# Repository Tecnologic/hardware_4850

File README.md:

# Jacobi
36 V / 45 A (battery side, 100 A peak phase current) drive hardware of the [unimoc](https://github.com/Tecnologic/unimoc)
project, with optimised cooling. Jacobi is the motor controller (logic board and
power board); the firmware lives in the unimoc repository.

| | |
|---|---|
| Board directory (firmware) | `boards/unimoc/jacobi/` |
| Board name | `unimoc_jacobi` |
| Cyphal node name | `org.unimoc.jacobi` |
| EESM variant | Jacobi E |

Formerly `hardware_4850`.

### Naming

The unimoc nodes are named after inventors. Moritz Hermann Jacobi built the
first practical electric motor (1834, Königsberg) and drove a boat on the Neva
with it (1838): the first electric motor put to practical use as a drive, which
is what this board is for.

**Drives**

| Name | Class | Who |
|---|---|---|
| Barlow | small drive | Peter Barlow, whose "Barlow's wheel" (1822) was one of the first electric motors: tiny but turning |
| **Jacobi** | **36 V / 45 A drive (this board, H7)** | Moritz Hermann Jacobi, first practical electric motor (1834) and electric boat on the Neva (1838) |
| Dolivo | big drive | Michail Dolivo-Dobrowolsky invented the three-phase motor and the three-phase system (AEG, 1889), the basis of every FOC drive |

**Other nodes**

| Name | Role | Who |
|---|---|---|
| Zuse | VDC | Konrad Zuse built the first working programmable computer, so he's the brain |
| Drais | Pedal generator | Karl Drais invented the Laufmaschine (1817), the ancestor of the bicycle, powered by your own feet |
| Mercator | Steering | the map maker everyone navigates by |
| Gutenberg | Display | made information visible to everyone |
| Volta | BMS / battery | invented the battery (the voltaic pile, 1800) |
| Otto | Throttle | Nikolaus Otto, of the Otto engine: the classic gas pedal |

## Ratings and limits

What the hardware can do and where it stops. The numbers come from the
datasheets and rough loss and thermal estimates (calculations below), not from
measurements on a test bench. The reference load is the kids' quad: an MY1020
1600 W BLDC on 3 × 12 V lead-acid, which the controller already drives with
80 A peak phase current.

| | Rating | Limited by |
|---|---|---|
| Battery | **3 × 12 V lead-acid (36 V)**, up to 44 V while charging; Li-ion up to 10S (42 V) | 60 V FETs (NCEP6080AG), see below |
| Enable input (J501 pin 3 against pin 4) | **12–40 V**, switched battery voltage; 1–4 mA through a TLP291 optocoupler, 3750 Vrms isolation | input resistor R1115 (10k, 1206): 0.19 W at 44 V, 0.25 W rating |
| Battery current | **~45 A** (1600 W at 36 V) for minutes in still air; continuous only with better cooling | housing to air: 1600 W needs about 58 A peak phase current |
| Phase current, peak | **100 A** for seconds | motor saturation, FET losses |
| Phase current, continuous | **~50 A peak** in still air; with the housing bolted to a frame or in airflow, the 100 A motor limit comes first | housing to air (about 2.5 K/W) |
| Overcurrent trip | **120–130 A** | current sensing range ±160 A |
| Not suitable for | 48 V systems (13S/14S Li-ion, 4 × 12 V lead-acid) | 60 V FET rating |

### Target motors

| Motor | Saturation (peak phase current) | Fit |
|---|---|---|
| 60 mm stator motors | ~100 A | up to the rating |
| Hoverboard hub motors | ~55 A | about a third of the current range, fine resolution |
| MY1020 1600 W, 36 V (kids' quad) | not published, estimated 80–100 A | runs today at 80 A peak |

The MY1020 has no published saturation data. It can be measured with the
controller: lock the rotor, run a DC current on the d or q axis in steps
(0, 20, 40 … 120 A) and measure L = V / (di/dt) with a small voltage pulse.
Saturation starts where L falls by 20–30 %. Above that current the motor gives
little extra torque and mostly heat, so it is the useful current limit.

### Bridge voltage: why 36 V

The bridge uses **NCEP6080AG** (NCE, LCSC `C182469`, DFN5×6-8L), two in
parallel per switch, 12 per board. They are in stock and cost much less than
an 80 V part. From the LCSC product page (the datasheet PDF was not
reachable): 60 V, 80 A, R_DS(on) < 4.0 mΩ at 10 V (3.5 mΩ typ),
< 5.0 mΩ at 4.5 V, Qg 67 nC, Coss 680 pF, 85 W, Tj up to 150 °C.

| Battery | Max voltage | Margin to 60 V |
|---|---|---|
| 3 × 12 V lead-acid | ~44 V (charging) | 16 V: **fine** |
| 10S Li-ion | 42 V | 18 V: **fine** |
| 13S Li-ion | 54.6 V | 5 V: switching overshoot alone can use that, **no** |
| 14S Li-ion / 4 × 12 V | 58.8 V / ~58 V | **no** |

For 48 V the bridge needs 80 V FETs in the same footprint, e.g. the Infineon
**BSC040N08NS5** (80 V, 4.0 mΩ max, 121 A, marking `040N08NS`), which sits on
one of the existing prototype boards. Its R_DS(on) is the same as the NCE part;
its lower gate charge (43 nC) only shortens the switching edges a little. The
rest of the board already handles 48 V: the LM5008 supply runs from the battery
up to 95 V, and the voltage dividers reach 73.8 V full scale.

### Bridge losses

Two FETs in parallel per switch, sine current, 36 V, 20 kHz PWM, about 45 ns
switching edges (LM5109B at about 1 A into 2 × 67 nC, 1R1 gate resistors).
R_DS(on) is 4.0 mΩ max × 1.6 for Tj = 125 °C ≈ 6.4 mΩ. The factor 1.6 is
taken from the BSC040N08NS5 curve because the NCE datasheet was not
available; check it once the datasheet is in `datasheets/`.

| Phase current (peak) | Loss per FET | Loss per phase | Whole bridge |
|---|---|---|---|
| 50 A | ~1.3 W | ~5 W | ~16 W |
| 80 A | ~3 W | ~12 W | ~36 W |
| 100 A | ~4.5 W | ~18 W | ~54 W |

Conduction per FET is I_rms² × R_DS(on) / 8 (the phase current splits over two
FETs, and high and low side each conduct about half the time). Switching per
phase is ½ × V × I_avg × (t_on + t_off) × f_PWM with I_avg = 2/π × I_peak.

Using one FET per switch instead of two would save 6 FETs and about 180 mm²,
but it doubles the conduction loss at the same current (about 16 W per FET at
100 A peak). In the closed housing that comes straight off the continuous
current, so the board keeps two per switch.

### PCB manufacturing

The board is made by JLCPCB: 4 layers, **1 oz copper** on all layers (outer and
inner), standard process. The design rules in `jacobi.kicad_pro` follow the
[JLCPCB 4-layer capabilities](https://jlcpcb.com/capabilities/pcb-capabilities):

| Rule | Value |
|---|---|
| Min track width / clearance | 0.1 mm / 0.1 mm |
| Min via (diameter / drill) | 0.45 mm / 0.2 mm, annular ring 0.125 mm |
| Min copper to board edge | 0.3 mm |
| Min hole to hole / hole clearance | 0.25 mm |
| Min silk text | 1.0 mm high, 0.15 mm line |

Net classes set the routing defaults (the high-current nets use pours, the track
width is only for stubs and pad entries):

| Class | Track / clearance / via | Nets |
|---|---|---|
| Power | 1.0 / 0.25 / 0.8 ⌀ 0.4 mm | +BATT, GNDPWR, phase and switch nodes |
| GateDrive | 0.5 / 0.2 / 0.6 ⌀ 0.3 mm | +12P, gate, HO/LO/HS/VSS, bootstrap |
| Dig Supply | 0.4 / 0.2 / 0.6 ⌀ 0.3 mm | +12V, +3V3, +1V2, +BATT_LOGIC, GNDD, buck nodes |
| Analog Supply | 0.4 / 0.2 / 0.6 ⌀ 0.3 mm | +3.3VA, +3.3VADC, GNDA, GND |
| Analog | 0.2 / 0.2 / 0.45 ⌀ 0.2 mm | current and voltage sense, temperature, ADC inputs |
| USB | 0.2 / 0.2 mm, pair gap 0.15 mm | USB_DP, USB_DM (impedance not yet checked) |
| Default | 0.15 / 0.15 / 0.45 ⌀ 0.2 mm | everything else |

### Cooling

The power board sits on an aluminium block the size of the board, which is
mounted to the floor of the G113T housing (115 × 90 mm). Today the bottom
copper is covered by solder mask, with thermal paste to the block and a
thermal pad to the housing.

| Step (per FET unless noted) | Rth | Note |
|---|---|---|
| Junction → case | ~1 K/W | datasheet class value |
| **Thermal vias** | **~3.3 K/W** | 38 × 0.4 mm, 25 µm plating: the largest step from FET to block |
| Solder mask + paste | ~1 K/W | 20 µm mask, 50 µm paste over about 100 mm² |
| Junction → block | **~5.5 K/W** | about 17 K at 80 A peak, about 25 K at 100 A peak |
| Block → housing (pad, whole board) | 0.05–0.1 K/W | 3–5 K at 54 W |
| **Housing → air (whole board)** | **~2–3 K/W** | 0.043 m² of housing in still air: **sets the continuous current** |

At 80 A peak the bridge loses about 36 W. In still air the housing would end up
far above any sensible temperature; it works because the peaks are short. The
block and housing hold about 600 J/K (10 mm block assumed), a time constant of
about 25 minutes, so 54 W (100 A peak) heats them by about 5 K per minute.

Continuous current for a block at ≤ 80 °C at 40 °C ambient (40 K):

| Housing to air | Allowed loss | Continuous phase current |
|---|---|---|
| Still air, ~2.5 K/W | ~16 W | ~50 A peak |
| Bolted to the frame or in airflow, ~0.5 K/W | ~80 W | ~120 A peak, so the 100 A motor limit comes first |

Improvements, biggest first:

1. **Housing to air.** Bolt the housing to the vehicle frame or a metal plate
   with paste, or add fins or airflow. This is worth more than all other steps
   together.
2. **Thermal vias.** Filled and capped vias (VIPPO) under the drain pad, as many
   as fit: about half the 3.3 K/W. The board stays 1 oz copper; the currents are
   carried by pours on all four layers, not by thicker copper.
3. **Block to housing.** Thin paste on flat surfaces instead of the thermal pad,
   screws near the FET rows.
4. **Copper spreading.** Large drain pours under each FET on the bottom and
   inner layers.

**Keep the isolation.** The bottom copper under the high-side FETs is at
+BATT, under the low-side FETs it is the phase node, and the block conducts.
The solder mask is the only insulation today. Opening the mask needs a defined
insulator instead (25 µm polyimide film or a 0.15–0.2 mm ceramic-filled pad);
thermally that is about the same as mask and paste, but the isolation is
reliable. Avoid metal-filled pastes there.

### Current sensing

One 0.5 mΩ 3920 shunt per phase (Yezhan DSLR-M-5-0.5F) in the phase output,
with an INA240A1 (gain 20):

| | |
|---|---|
| Range | 1.6 V / (20 × 0.5 mΩ) = **±160 A**, 10 mV/A |
| Overcurrent trip | 120–130 A, above the 100 A motor saturation |
| Offset | 25 µV max at the input = 0.05 A; calibrated at start, drift 0.25 µV/K |
| Resolution | about 0.08 A at 12 effective bits |
| Shunt loss | 1.6 W at 80 A peak, 2.5 W at 100 A peak (9 W part) |

Other combinations that were considered:

| Shunt + INA240 | Range | Why not |
|---|---|---|
| 0.4 mΩ + A1 | ±200 A | only needed for currents above 130 A, which the motors cannot use |
| 0.2 mΩ + A2 | ±160 A | same scaling, but 2.5× the offset in amps, and the A2 costs 1.60 € vs 0.25 € for a shunt |
| 0.2 mΩ + A1 | ±400 A | coarse at light load (about 0.2 A noise) |

## KiCad project

The logic board and the power board are combined in a single **KiCad 10** project:
[`jacobi.kicad_pro`](jacobi.kicad_pro).

| File | Content |
|---|---|
| [`jacobi.kicad_sch`](jacobi.kicad_sch) | Root sheet with the two board sheets |
| [`logic.kicad_sch`](logic.kicad_sch) | Logic board: sub-sheets [`power_supply`](power_supply.kicad_sch) and [`controller`](controller.kicad_sch); `controller` has the sub-sheets [`interfaces`](interfaces.kicad_sch) and [`analog`](analog.kicad_sch) |
| [`power.kicad_sch`](power.kicad_sch) | Power board: sub-sheet [`phase`](phase.kicad_sch), used three times for phase A/B/C |
| [`jacobi.kicad_pcb`](jacobi.kicad_pcb) | Both boards side by side: logic board on the left, power board on the right |
| [`footprints/jacobi.pretty`](footprints/jacobi.pretty) | Project footprint library: enclosure RND 455-00370, the Kelvin footprint of the phase shunt `R_Shunt_Yezhan_DSLR-5_3920_Kelvin`, and `LFPAK56_ThermalVias-1` and `C_2220_5650Metric`, which KiCad 10 no longer ships |

Since both boards are in one PCB file, the net names are kept apart by the
schematic hierarchy (`/logic/...`, `/power/...`). The board-to-board connectors
(J101/J102/J111 on the logic board, J103/J104/J110 on the power board) are **not** joined
electrically in the schematic, so each board keeps its own nets.

## Schematic ahead of the PCB

The schematic is ahead of the PCB. The logic board will be laid out again;
the PCB still shows the old F730 board.

- **MCU: STM32H743VIT6** (LQFP100, 2 MB flash, LCSC `C114409`) instead of the
  STM32F730R8. It sits on the `controller` sheet (now A3) and connects by net
  labels; the old wires end in labels of the same names. Added decoupling
  C613–C622; C603 is now 2.2 µF (VCAP). Pin plan and open points:
  [docs/h743_logic_board.md](docs/h743_logic_board.md).
- **Simple analog front end.** The op-amp filters of the logic board are gone
  (the three `current_filters` sheets with low pass and AC high pass per phase,
  and the U701 filters for Vdc and the bridge NTC). What is left on the `analog`
  sheet:
  - Ia/Ib/Ic: 220R / 2n2 RC from the INA240 outputs (R717–R719, C713–C715)
  - Va/Vb/Vc: 220R / 2n2 RC (R720–R722, C716–C718), the same as the currents
  - Vdc: 4k7 / 10n RC (R705/C704)
  - +12P (gate driver supply): 4k7 / 10n RC (R723/C719)
  - bridge NTC: pull-up R703 with C701, then a 4k7 / 10n RC (R704/C703)
  - motor temperature unchanged

  The filter values are a first guess.
- **Voltage sensing on the power board.** The dividers for the phase voltages
  and Vdc (47k / 2k2 0.1 %, with 1 nF; R101–R108, C101–C104) sit on the power
  board and go to the logic board over a third 2×5 connector, J110 → J111
  (VSENSE). The old Vdc divider R701/R702/C702 on the logic board is gone.
- **Gate driver supply sense.** A 10k / 2k2 divider (R109/R110, C105) on +12P
  at the drivers goes over pin 3 of the PWM connector (J103 → J101) to PC5. No
  12 V is routed to the analog part.
- **Power board present.** J110 pin 9 is GND on the power board; on the logic
  board it is pulled up (R612, 10k) to PE4 (`PWR_DET`, low = present).
- **Bridge NTC to GND on the power board.** TH101 has its low side on the power
  board GND; only the high side goes through J104 pin 8. J104 pin 10 is now GND.
- **One shunt per phase.** 0.5 mΩ 3920 (Yezhan DSLR-M-5-0.5F, LCSC
  `C41382689`) with Kelvin sense pads instead of three 2 mΩ 2512 in
  parallel, read by an INA240A1 (gain 20): ±160 A.
- **USB-C** instead of mini-B: HRO TYPE-C-31-M-12 (LCSC `C165948`, 16 pins,
  USB 2.0), 5k1 on CC1/CC2 (R613/R614) as a device. SBU not connected.
- **PWM_EN through an optocoupler.** The PWM_EN jumper J1102 is gone. The
  enable input is a TLP291 (U1102) on the `interfaces` sheet that pulls PE15
  high. J501 (`Enable`, now 4-pin JST PH) carries, from pin 1: `+BATT_LOGIC`
  (battery +), the LM5008 supply (VIN), `PWM_EN_IN` (opto LED +, **12–40 V**)
  and `PWM_EN_RTN` (opto LED return, battery −). The LED path is 10k (R1115)
  with 10n (C1108) across the LED and a 1N4148W (D1105) against reverse
  polarity. The output has a 510R collector resistor, a 10k pulldown (R1116)
  and 10n (C1109). `PWM_EN_RTN` is not connected to `GNDD`, so the enable
  line is isolated and its current stays in its own wire pair, which keeps
  noise out on a cart with four drives. Keep the LED side clear of copper from
  the output side under U1102 (5 mm creepage). On the bench bridge pins 1–2,
  put battery + on pin 3 and battery − on pin 4. On the cart switch pin 2
  (logic) and pin 3 (phases).
- **`+48V` is now `+BATT_LOGIC`.** The board is no longer 48 V compatible
  (60 V FETs), so the logic board supply net (J101 pin 1, J501 pin 1) is named
  after the battery. It stays a separate net from `+BATT` on the power board.
- **No aux bridge.** The EESM excitation and brake chopper are out of scope for
  this board; a separate module will do that.

## Production data

The production files of the PCB contain both boards. For separate production
data per board, the old KiCad 5 data is in
[`production/legacy_kicad5/`](production/legacy_kicad5) (as manufactured, with
the op-amp filters, and the 2020 logic board BOM with prices).

## Other folders

| Folder | Content |
|---|---|
| [`datasheets/`](datasheets) | Component datasheets |
| [`docs/`](docs) | Pictures of the [logic board](docs/logic_board.png) and the [power board](docs/power_board.png) (old F730 boards), [H743 logic board concept](docs/h743_logic_board.md) |
| [`mechanical/`](mechanical) | DXF exports of the power board, the cooler drawing, [`enclosure/`](mechanical/enclosure) with STEP and DXF views of the RND 455-00370 |
| [`nucleo_adapter/`](nucleo_adapter) | Bench adapter: a NUCLEO-H743ZI drives the legacy 4850 power board in place of the old logic board (own KiCad project, see its [README](nucleo_adapter/README.md)) |

## Conversion notes (KiCad 5.1 → KiCad 10)

- All symbols are updated from the KiCad 10 library; no KiCad 5 symbol
  graphics are left. The unused `SolderJumper_2_Open` was dropped. The old
  bitmaps of the other board on the `logic` and `power` sheets are removed.
- The KiCad 5 schematic had other values than the PCB on the power board (the
  PCB was changed later). The schematic now follows the PCB: Q`x`01–Q`x`04
  `NCEP6080AG`, C`x`07/C`x`09 `56u`, R`x`03–R`x`10 `1R1`. Their old `Part#`
  order numbers were removed and still have to be filled in.
- Parts that KiCad 10 dropped or renamed:
  - Footprints `LFPAK56_ThermalVias-1` and `C_2220_5650Metric` are now in the
    project library, copied from the PCB.
  - The 3D model of the 2220 capacitor now points to `C_2220_5750Metric`.
  - Symbols are relinked: `Device:CP` → `Device:C_Polarized`,
    `Device:Ferrite_Bead_Small` → `Device:FerriteBead_Small`,
    `Device:Jumper_NO_Small` → `Jumper:Jumper_2_Small_Open`.

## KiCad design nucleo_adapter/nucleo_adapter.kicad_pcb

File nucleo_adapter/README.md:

# Nucleo adapter for the legacy 4850 power board

A bench adapter that lets a **NUCLEO-H743ZI** (first revision, MB1137, silicon
rev. Y) drive the **legacy 4850 power board**, the one ordered on 2019-11-20
(`production/legacy_kicad5/power`). It takes the place of the old STM32F730
logic board, so the H7 hot path of the unimoc firmware can run against the
real INA240 stage before Jacobi exists. The power stage itself is not part of
this design.

KiCad 10 project: `nucleo_adapter.kicad_pro`. Status: **draft, not routed, not
reviewed**. The schematic and the PCB are generated (see `tools/`) and pass
ERC and DRC with schematic parity. Only the 167 unrouted connections are left.

## What lines up with the power board

The PCB uses the coordinate system of the legacy power board, so you can
overlay the two files (`production/legacy_kicad5/power`, KiCad 5 PCB of commit
`d914cf3`, which matches the Gerbers exactly).

| Adapter | Power board | Position (mm) | Note |
|---|---|---|---|
| J101 PWM, SMD 2x05 pin header, bottom | J103, SMD 2x05 socket | (64.5, 120.75), rot 90 | Copied from the old logic board's J101 |
| J102 ADC, SMD 2x05 pin header, bottom | J104, SMD 2x05 socket | (125.0, 130.0), rot -90 | Copied from the old logic board's J102 |
| H101, M3 | H105 | (99.75, 106.75) | Standoff |
| H102, M3 | H104 | (70.0, 178.5) | Standoff |
| H103, M3 | H107 | (122.0, 178.5) | Standoff |
| (no hole) | H106 | (100.25, 157.5) | Heatsink bolt; outline on `User.Drawings` |

These footprints are locked. The generator checked every pad against the old
logic board and every pin against the power-board socket: all 20 pins mate
with the intended signal (table below). The power-board area keeps the old
logic board's 8 x 8 mm notches at the far corners. `User.Drawings` shows the
84 x 79 mm power-board outline.

The current Jacobi PCB keeps the holes H101-H107 where they were, but moves
J101/J102 and adds J110/J111 (VSENSE). **This adapter fits only the legacy
power board.**

### Connector pinout (from the as-ordered power board)

| Pin | J101 PWM | | J102 ADC | |
|---|---|---|---|---|
| 1 | +BATT (DC link, only sensed here) | | +3.3VA (INA240 V+ and REF2) | |
| 2 | GND (= GNDPWR) | | I_C | INA240 out, phase C |
| 3 | open on the power board | | GNDA (power-board GND) | |
| 4 | PWM_AH | LM5109B HI, phase A | I_B | |
| 5 | +12V (gate driver VDD, from the adapter) | | GNDA | |
| 6 | PWM_AL | | I_A | |
| 7 | PWM_CL | | GNDA | |
| 8 | PWM_BH | | T_BRIDGE (NTC TH101, high side) | |
| 9 | PWM_CH | | GNDA | |
| 10 | PWM_BL | | GNDA (NTC low side) | |

INA240A1 on the power board: V+ and REF2 on +3.3VA, REF1 on GND, so
`I_x = 1.65 V + 20 mV/A`. With two 2 mΩ shunts in parallel per phase that is
about ±80 A full scale. No scaling is needed for the 3.3 V ADC.

## Board

- Outline: 100 x 221 mm in total. The power-board area is x 57..141,
  y 103..182 (84 x 79). The Nucleo part is x 49..149, y -39..103.
- 4 layers, with the design rules and the default net class of Jacobi (JLCPCB
  4-layer).
- The Nucleo (`U201`, footprint `Module:ST_Morpho_Connector_144_STLink_MountingHoles`)
  sits on the top side in two **2 x 36 female morpho sockets** (CN11, CN12).
  Footprint pads 1-144 are the symbol pins. Pads 145-148 at the ST-LINK end
  are not in the symbol: leave them empty.
- The morpho pins end 19 mm before the power-board edge, so no pin points
  down into the power stage. The ST-LINK USB is at the free end. The Nucleo's
  RJ45 end overhangs the power-board area above the adapter.
- Edge connectors (placed, not locked): J601 12 V in, J401 ENABLE, J503 HALL,
  J301 MOT_TEMP, J302 VPHASE on the left; J501/J502 CAN on the right.
- All other parts are parked to the right of the board, one column per sheet.

## Schematic

All sheets are A4. Hierarchy: root overview, then `power_board`, `nucleo`
(portrait), `analog` (currents, NTCs), `voltage` (Vdc and phase voltages),
`gate`, `interfaces` (CAN FD, Hall) and `supply`.

| Function | Nucleo pin | Circuit |
|---|---|---|
| PWM A/B/C high, low | PE9, PE11, PE13 / PE8, PE10, PE12 (TIM1) | 100R series, 10k pull-down at J101 |
| Break / enable | PE15 (TIM1_BKIN) | J401: close the loop to release; open = all outputs off |
| Ia, Ib, Ic | PA6, PB1, PC2_C | 220R / 2n2 |
| Vdc | PC3_C | 47k / 2k2 0.1 %, 1n (73.8 V full scale) |
| Va, Vb, Vc | PF11, PF13, PF10 | Same dividers, from J302 (wires to the phase pads J106-J108) |
| Bridge / motor temperature | PF12 / PF14 | 10k pull-up to +3.3VA, 1k / 100n |
| Hall A/B/C | PD12, PD13, PD14 | 2k2 pull-up to +3V3, 1k / 1n, sensors on +5V |
| CAN FD | PD0 RX, PD1 TX (FDCAN1) | TCAN334, JST GH 4 (Cyphal micro), 120R on JP501 |

The pin map is the one in the unimoc firmware,
`app/boards/nucleo_h743zi.overlay` on branch `hardware/first-startup`.

Supplies:

- **+12V** for the gate drivers comes from a bench supply on J601 (SS34
  reverse protection, SMAJ15CA clamp). It does not come from the DC link,
  because the first power-on runs the DC link at 12 V / 0.5 A.
- **+3.3VA** comes from the Nucleo +3V3 (VDDA, the ADC reference) through
  FB601, so the INA240 offset tracks the ADC reference.
- **GND and GNDA** meet only at FB602, as at FB502 on the old logic board. The
  power board does not join GND (GNDPWR) and its analog GND.

## To check before layout

1. LM5109B input threshold against 3.3 V logic (VIH in the datasheet).
2. Filter values (220R / 2n2, 1k / 100n) are first guesses.
3. Clearance under the adapter: the old logic board had the same stack height
   (SMD socket on the power board, SMD header on the bottom here). The
   bottom side over the power board should stay free of tall parts.
4. Mounting-hole and standoff heights against the socket height of J103/J104.
5. Whether J101 pin 3 should carry anything. It is open on the power board.
6. Phase-voltage wires on J302: only needed for identification step I3.
7. Firmware: the Nucleo overlay has no `PWM_EN` GPIO. Here the enable is the
   break loop on PE15.

## Tools

`tools/` holds the one-shot generator that made the first version:
`design.py` (the netlist as data), `gen_sch.py`, `gen_pcb.py` (KiCad 10
pcbnew), `gen_pro.py`, `checknet.py`. The KiCad files are the source from now
on. Edit them in KiCad and do not regenerate over manual work.

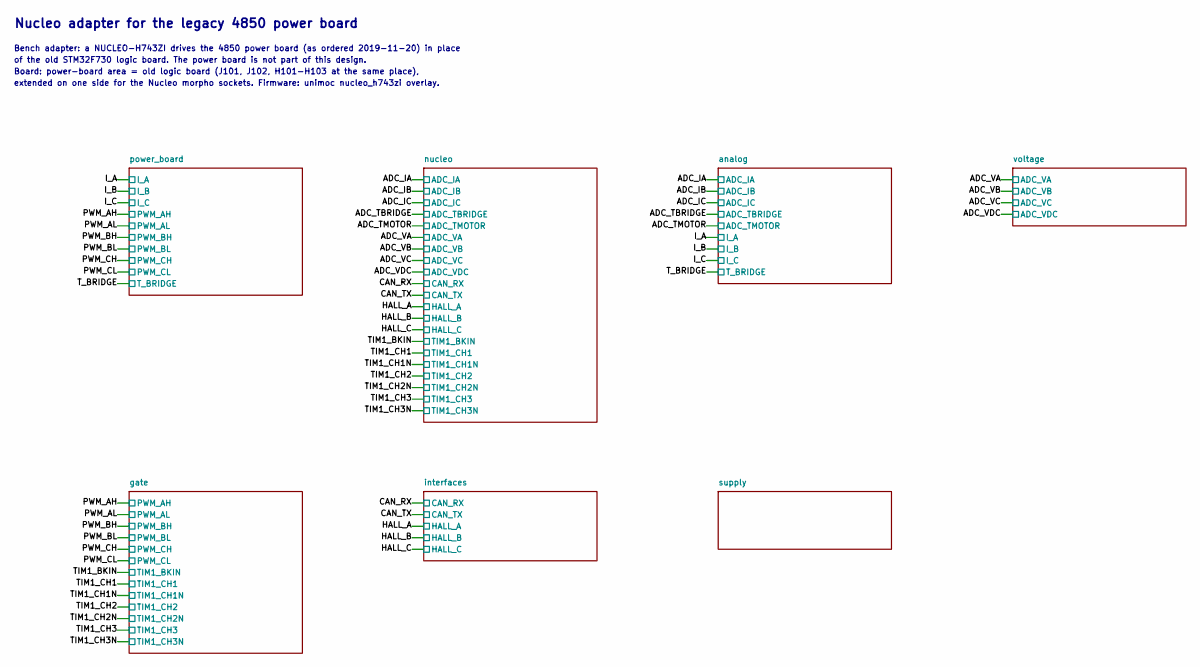
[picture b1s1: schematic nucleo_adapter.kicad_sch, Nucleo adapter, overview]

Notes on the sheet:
Bench adapter: a NUCLEO-H743ZI drives the 4850 power board (as ordered 2019-11-20) in place
of the old STM32F730 logic board. The power board is not part of this design.
extended on one side for the Nucleo morpho sockets. Firmware: unimoc nucleo_h743zi overlay.
Nucleo adapter for the legacy 4850 power board
Board: power-board area = old logic board (J101, J102, H101-H103 at the same place),

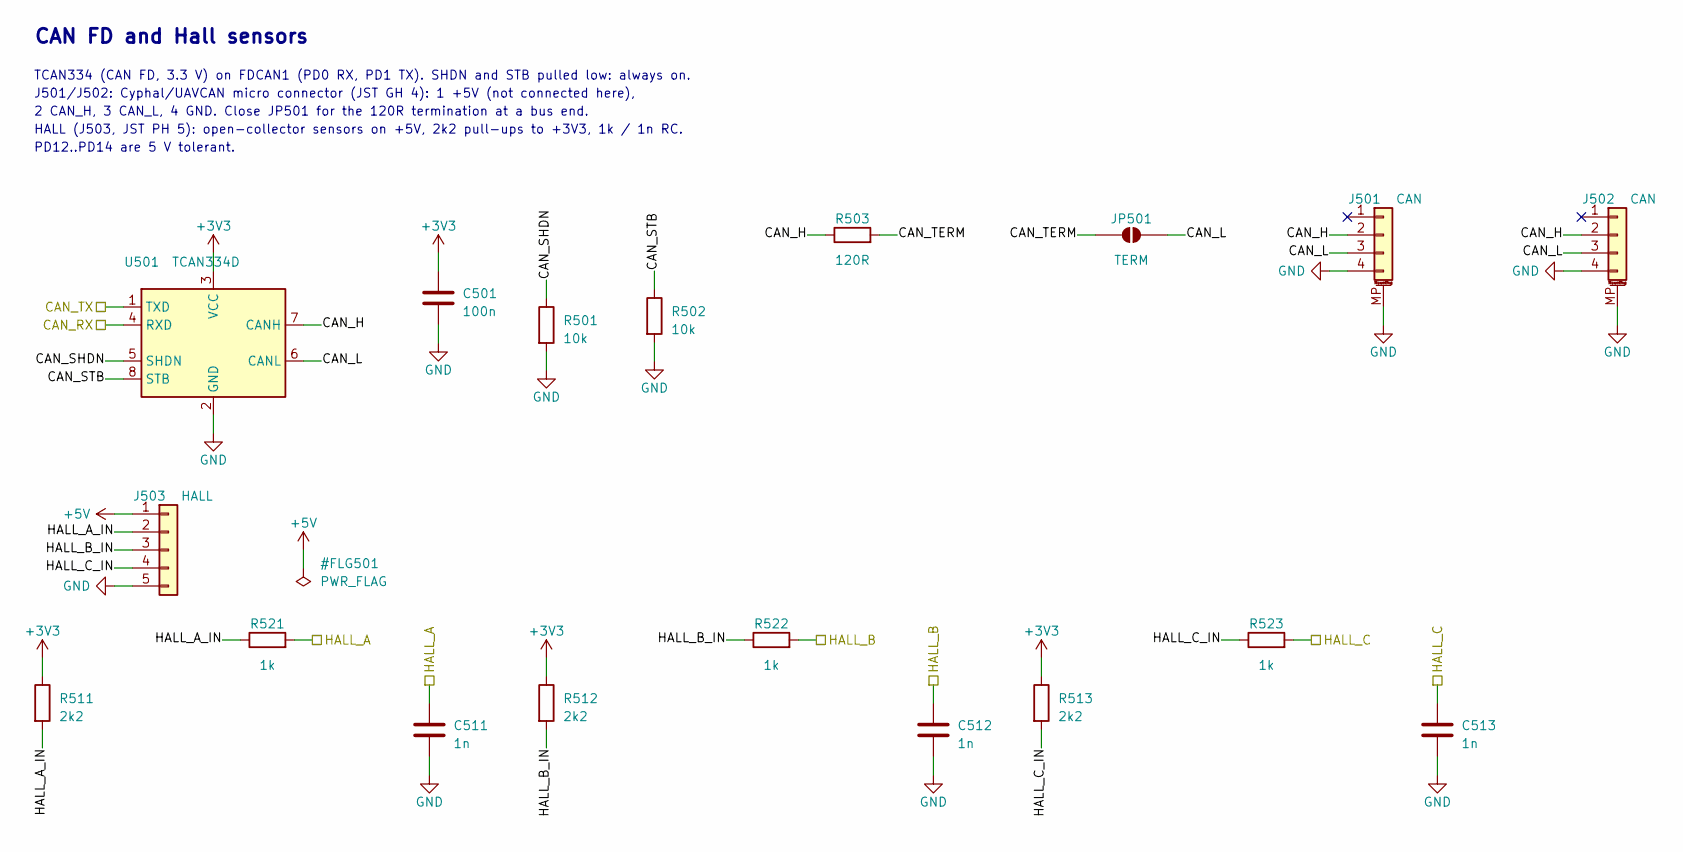
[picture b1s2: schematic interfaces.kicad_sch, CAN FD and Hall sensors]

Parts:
C501: 100n; C_0603_1608Metric
C511, C512, C513: 1n; C_0603_1608Metric
J501, J502: CAN; JST_GH_SM04B-GHS-TB_1x04-1MP_P1.25mm_Horizontal
J503: HALL; JST_PH_B5B-PH-K_1x05_P2.00mm_Vertical
JP501: TERM; SolderJumper-2_P1.3mm_Open_RoundedPad1.0x1.5mm
R501, R502: 10k; R_0603_1608Metric
R503: 120R; R_0603_1608Metric
R511, R512, R513: 2k2; R_0603_1608Metric
R521, R522, R523: 1k; R_0603_1608Metric
U501: TCAN334D; SOIC-8_3.9x4.9mm_P1.27mm

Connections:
+3V3: C501.1, R511.1, R512.1, R513.1, U501.3 (VCC); also elsewhere on the board
+5V: J503.1; also elsewhere on the board
/CAN_RX: U501.4 (RXD); also elsewhere on the board
/CAN_TX: U501.1 (TXD); also elsewhere on the board
/HALL_A: C511.1, R521.2; also elsewhere on the board
/HALL_B: C512.1, R522.2; also elsewhere on the board
/HALL_C: C513.1, R523.2; also elsewhere on the board
/interfaces/CAN_H: J501.2, J502.2, R503.1, U501.7 (CANH)
/interfaces/CAN_L: J501.3, J502.3, JP501.2 (B), U501.6 (CANL)
/interfaces/CAN_SHDN: R501.1, U501.5 (SHDN)
/interfaces/CAN_STB: R502.1, U501.8 (STB)
/interfaces/CAN_TERM: JP501.1 (A), R503.2
/interfaces/HALL_A_IN: J503.2, R511.2, R521.1
/interfaces/HALL_B_IN: J503.3, R512.2, R522.1
/interfaces/HALL_C_IN: J503.4, R513.2, R523.1
GND: C501.2, C511.2, C512.2, C513.2, J501.4, J501.MP (MountPin), J502.4, J502.MP (MountPin), J503.5, R501.2, R502.2, U501.2 (GND); also elsewhere on the board

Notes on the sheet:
PD12..PD14 are 5 V tolerant.
2 CAN_H, 3 CAN_L, 4 GND. Close JP501 for the 120R termination at a bus end.
J501/J502: Cyphal/UAVCAN micro connector (JST GH 4): 1 +5V (not connected here),
CAN FD and Hall sensors
TCAN334 (CAN FD, 3.3 V) on FDCAN1 (PD0 RX, PD1 TX). SHDN and STB pulled low: always on.
HALL (J503, JST PH 5): open-collector sensors on +5V, 2k2 pull-ups to +3V3, 1k / 1n RC.

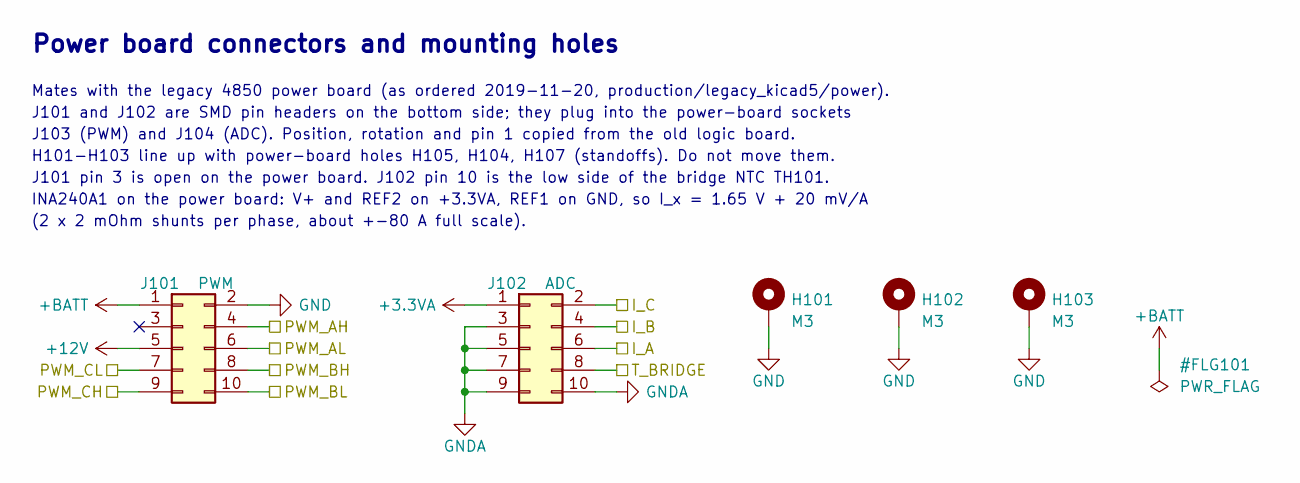
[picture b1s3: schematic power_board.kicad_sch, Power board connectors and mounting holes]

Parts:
H101: M3; MountingHole_3.2mm_M3_Pad_Via
H102, H103: M3; MountingHole_3.2mm_M3_ISO14580_Pad
J101: PWM; PinHeader_2x05_P2.54mm_Vertical_SMD
J102: ADC; PinHeader_2x05_P2.54mm_Vertical_SMD

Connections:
+3.3VA: J102.1; also elsewhere on the board
+12V: J101.5; also elsewhere on the board
+BATT: J101.1; also elsewhere on the board
/I_A: J102.6; also elsewhere on the board
/I_B: J102.4; also elsewhere on the board
/I_C: J102.2; also elsewhere on the board
/PWM_AH: J101.4; also elsewhere on the board
/PWM_AL: J101.6; also elsewhere on the board
/PWM_BH: J101.8; also elsewhere on the board
/PWM_BL: J101.10; also elsewhere on the board
/PWM_CH: J101.9; also elsewhere on the board
/PWM_CL: J101.7; also elsewhere on the board
/T_BRIDGE: J102.8; also elsewhere on the board
GND: H101.1, H102.1, H103.1, J101.2; also elsewhere on the board
GNDA: J102.3, J102.5, J102.7, J102.9, J102.10; also elsewhere on the board

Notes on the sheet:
INA240A1 on the power board: V+ and REF2 on +3.3VA, REF1 on GND, so I_x = 1.65 V + 20 mV/A
Mates with the legacy 4850 power board (as ordered 2019-11-20, production/legacy_kicad5/power).
(2 x 2 mOhm shunts per phase, about +-80 A full scale).
J101 and J102 are SMD pin headers on the bottom side; they plug into the power-board sockets
H101-H103 line up with power-board holes H105, H104, H107 (standoffs). Do not move them.
Power board connectors and mounting holes
J103 (PWM) and J104 (ADC). Position, rotation and pin 1 copied from the old logic board.
J101 pin 3 is open on the power board. J102 pin 10 is the low side of the bridge NTC TH101.

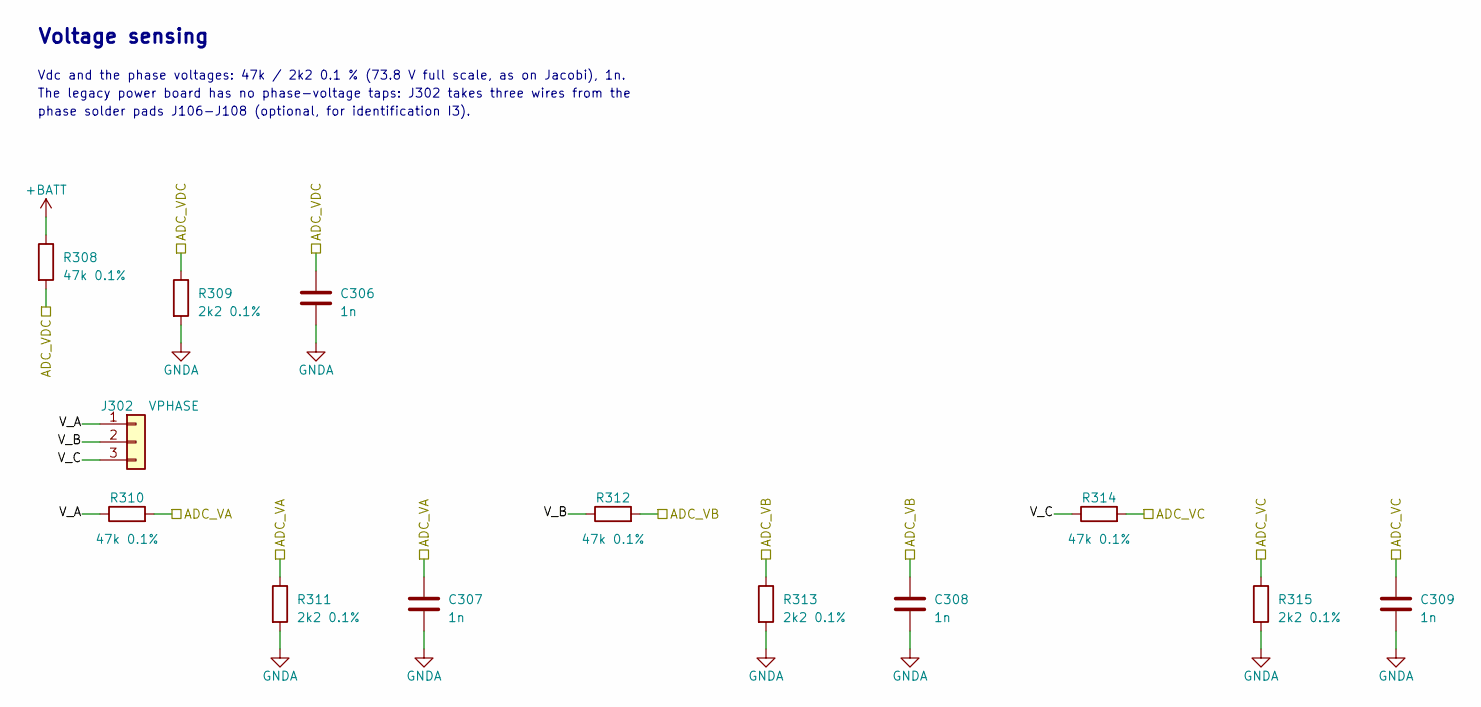
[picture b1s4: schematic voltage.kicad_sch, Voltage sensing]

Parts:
C306, C307, C308, C309: 1n; C_0603_1608Metric
J302: VPHASE; JST_PH_B3B-PH-K_1x03_P2.00mm_Vertical
R308, R310, R312, R314: 47k 0.1%; R_0603_1608Metric
R309, R311, R313, R315: 2k2 0.1%; R_0603_1608Metric

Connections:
+BATT: R308.1; also elsewhere on the board
/ADC_VA: C307.1, R310.2, R311.1; also elsewhere on the board
/ADC_VB: C308.1, R312.2, R313.1; also elsewhere on the board
/ADC_VC: C309.1, R314.2, R315.1; also elsewhere on the board
/ADC_VDC: C306.1, R308.2, R309.1; also elsewhere on the board
/voltage/V_A: J302.1, R310.1
/voltage/V_B: J302.2, R312.1
/voltage/V_C: J302.3, R314.1
GNDA: C306.2, C307.2, C308.2, C309.2, R309.2, R311.2, R313.2, R315.2; also elsewhere on the board

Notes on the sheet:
Vdc and the phase voltages: 47k / 2k2 0.1 % (73.8 V full scale, as on Jacobi), 1n.
The legacy power board has no phase-voltage taps: J302 takes three wires from the
Voltage sensing
phase solder pads J106-J108 (optional, for identification I3).

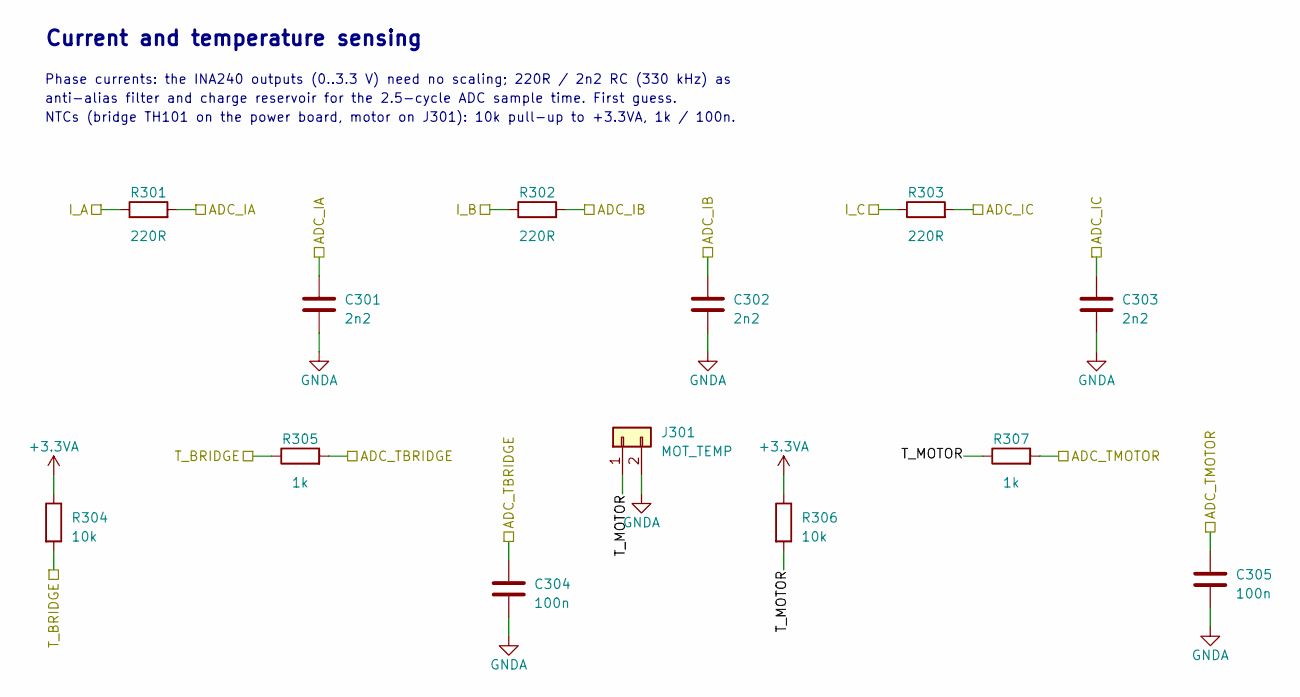
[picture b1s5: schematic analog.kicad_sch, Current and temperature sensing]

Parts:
C301, C302, C303: 2n2; C_0603_1608Metric
C304, C305: 100n; C_0603_1608Metric
J301: MOT_TEMP; JST_PH_B2B-PH-K_1x02_P2.00mm_Vertical
R301, R302, R303: 220R; R_0603_1608Metric
R304, R306: 10k; R_0603_1608Metric
R305, R307: 1k; R_0603_1608Metric

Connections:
+3.3VA: R304.1, R306.1; also elsewhere on the board
/ADC_IA: C301.1, R301.2; also elsewhere on the board
/ADC_IB: C302.1, R302.2; also elsewhere on the board
/ADC_IC: C303.1, R303.2; also elsewhere on the board
/ADC_TBRIDGE: C304.1, R305.2; also elsewhere on the board
/ADC_TMOTOR: C305.1, R307.2; also elsewhere on the board
/I_A: R301.1; also elsewhere on the board
/I_B: R302.1; also elsewhere on the board
/I_C: R303.1; also elsewhere on the board
/T_BRIDGE: R304.2, R305.1; also elsewhere on the board
/analog/T_MOTOR: J301.1, R306.2, R307.1
GNDA: C301.2, C302.2, C303.2, C304.2, C305.2, J301.2; also elsewhere on the board

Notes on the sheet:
anti-alias filter and charge reservoir for the 2.5-cycle ADC sample time. First guess.
Phase currents: the INA240 outputs (0..3.3 V) need no scaling; 220R / 2n2 RC (330 kHz) as
Current and temperature sensing
NTCs (bridge TH101 on the power board, motor on J301): 10k pull-up to +3.3VA, 1k / 100n.

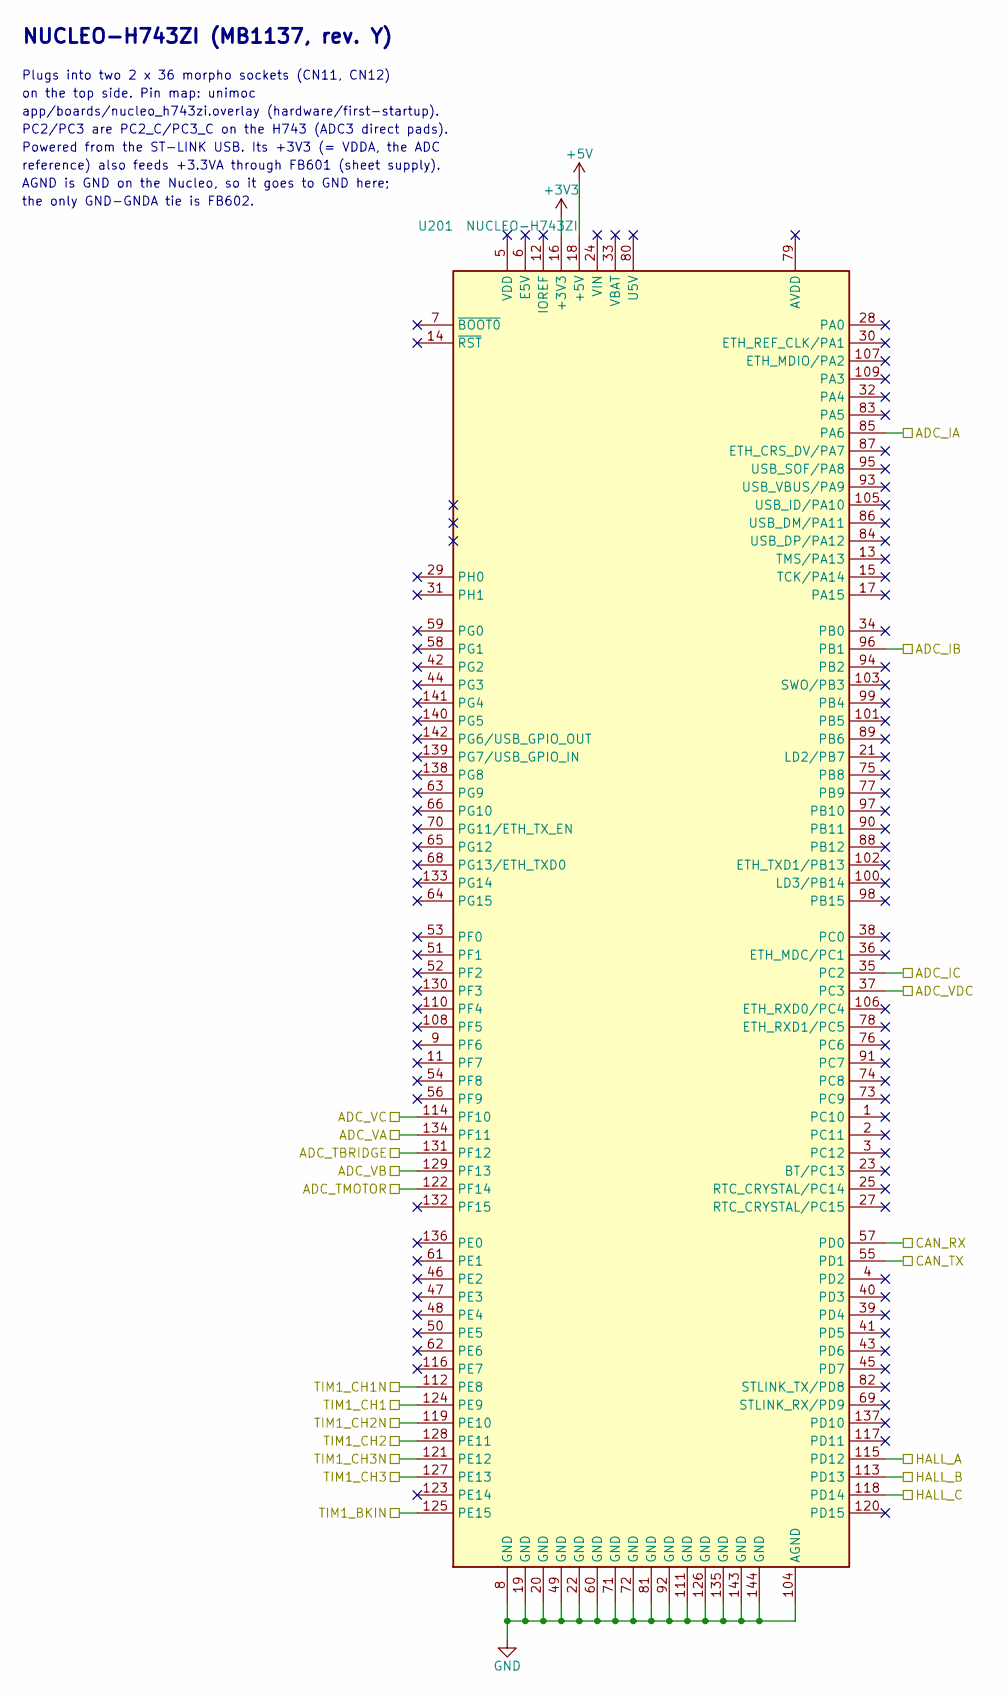
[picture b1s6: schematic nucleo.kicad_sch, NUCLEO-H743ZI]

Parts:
U201: NUCLEO-H743ZI; ST_Morpho_Connector_144_STLink_MountingHoles

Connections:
+3V3: U201.16 (+3V3); also elsewhere on the board
+5V: U201.18 (+5V); also elsewhere on the board
/ADC_IA: U201.85 (PA6); also elsewhere on the board
/ADC_IB: U201.96 (PB1); also elsewhere on the board
/ADC_IC: U201.35 (PC2); also elsewhere on the board
/ADC_TBRIDGE: U201.131 (PF12); also elsewhere on the board
/ADC_TMOTOR: U201.122 (PF14); also elsewhere on the board
/ADC_VA: U201.134 (PF11); also elsewhere on the board
/ADC_VB: U201.129 (PF13); also elsewhere on the board
/ADC_VC: U201.114 (PF10); also elsewhere on the board
/ADC_VDC: U201.37 (PC3); also elsewhere on the board
/CAN_RX: U201.57 (PD0); also elsewhere on the board
/CAN_TX: U201.55 (PD1); also elsewhere on the board
/HALL_A: U201.115 (PD12); also elsewhere on the board
/HALL_B: U201.113 (PD13); also elsewhere on the board
/HALL_C: U201.118 (PD14); also elsewhere on the board
/TIM1_BKIN: U201.125 (PE15); also elsewhere on the board
/TIM1_CH1: U201.124 (PE9); also elsewhere on the board
/TIM1_CH1N: U201.112 (PE8); also elsewhere on the board
/TIM1_CH2: U201.128 (PE11); also elsewhere on the board
/TIM1_CH2N: U201.119 (PE10); also elsewhere on the board
/TIM1_CH3: U201.127 (PE13); also elsewhere on the board
/TIM1_CH3N: U201.121 (PE12); also elsewhere on the board
GND: U201.8 (GND), U201.19 (GND), U201.20 (GND), U201.22 (GND), U201.49 (GND), U201.60 (GND), U201.71 (GND), U201.72 (GND), U201.81 (GND), U201.92 (GND), U201.104 (AGND), U201.111 (GND), U201.126 (GND), U201.135 (GND), U201.143 (GND), U201.144 (GND); also elsewhere on the board

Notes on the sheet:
NUCLEO-H743ZI (MB1137, rev. Y)
on the top side. Pin map: unimoc
Plugs into two 2 x 36 morpho sockets (CN11, CN12)
AGND is GND on the Nucleo, so it goes to GND here;
the only GND-GNDA tie is FB602.
app/boards/nucleo_h743zi.overlay (hardware/first-startup).
PC2/PC3 are PC2_C/PC3_C on the H743 (ADC3 direct pads).
Powered from the ST-LINK USB. Its +3V3 (= VDDA, the ADC
reference) also feeds +3.3VA through FB601 (sheet supply).

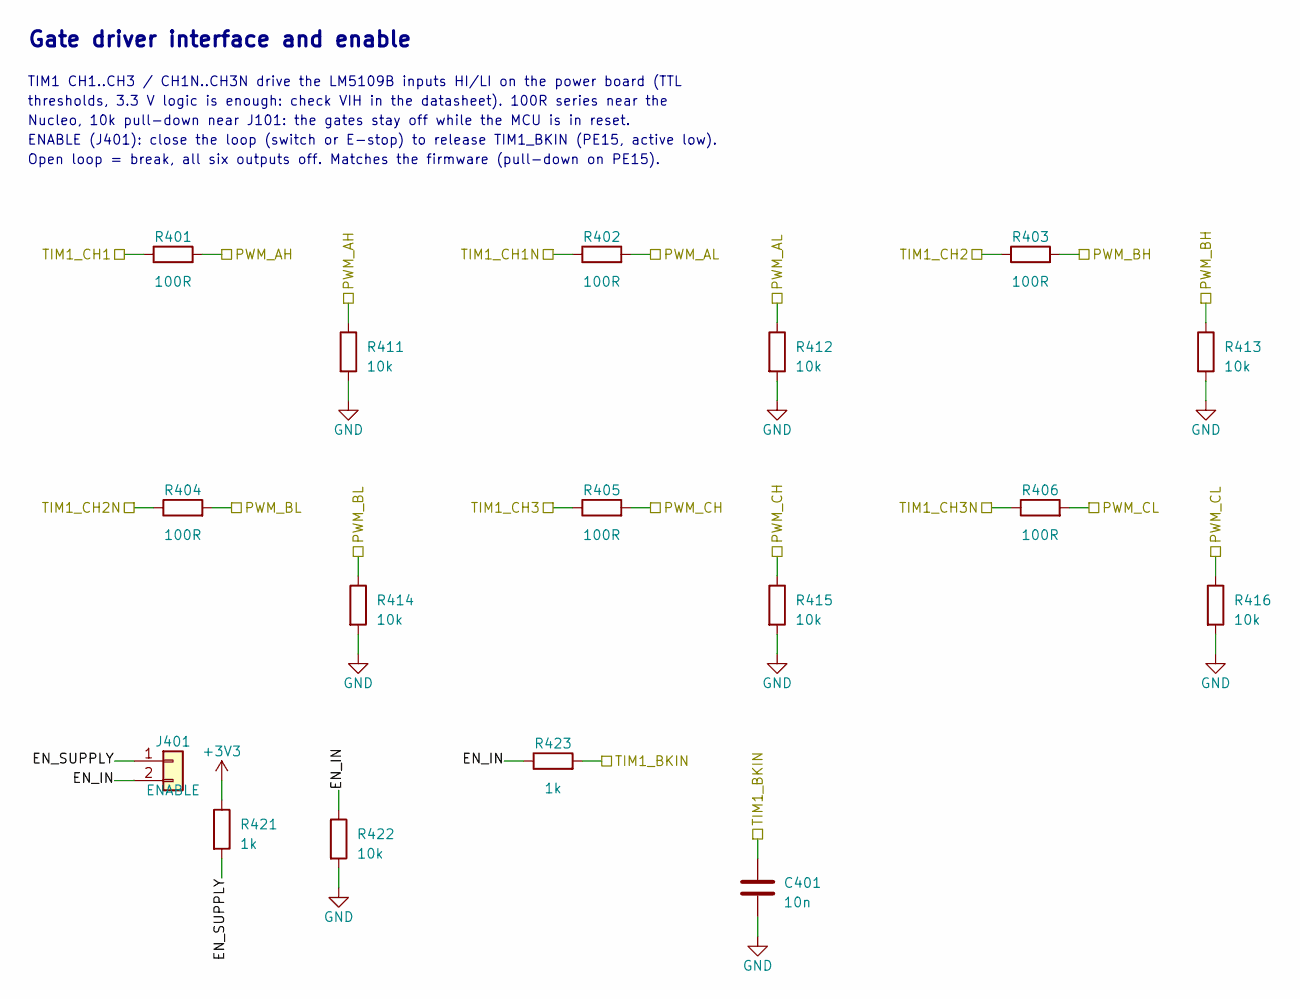
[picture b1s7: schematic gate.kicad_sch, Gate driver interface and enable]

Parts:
C401: 10n; C_0603_1608Metric
J401: ENABLE; JST_PH_B2B-PH-K_1x02_P2.00mm_Vertical
R401, R402, R403, R404, R405, R406: 100R; R_0603_1608Metric
R411, R412, R413, R414, R415, R416, R422: 10k; R_0603_1608Metric
R421, R423: 1k; R_0603_1608Metric

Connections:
+3V3: R421.1; also elsewhere on the board
/PWM_AH: R401.2, R411.1; also elsewhere on the board
/PWM_AL: R402.2, R412.1; also elsewhere on the board
/PWM_BH: R403.2, R413.1; also elsewhere on the board
/PWM_BL: R404.2, R414.1; also elsewhere on the board
/PWM_CH: R405.2, R415.1; also elsewhere on the board
/PWM_CL: R406.2, R416.1; also elsewhere on the board
/TIM1_BKIN: C401.1, R423.2; also elsewhere on the board
/TIM1_CH1: R401.1; also elsewhere on the board
/TIM1_CH1N: R402.1; also elsewhere on the board
/TIM1_CH2: R403.1; also elsewhere on the board
/TIM1_CH2N: R404.1; also elsewhere on the board
/TIM1_CH3: R405.1; also elsewhere on the board
/TIM1_CH3N: R406.1; also elsewhere on the board
/gate/EN_IN: J401.2, R422.1, R423.1
/gate/EN_SUPPLY: J401.1, R421.2
GND: C401.2, R411.2, R412.2, R413.2, R414.2, R415.2, R416.2, R422.2; also elsewhere on the board

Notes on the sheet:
Open loop = break, all six outputs off. Matches the firmware (pull-down on PE15).
thresholds, 3.3 V logic is enough: check VIH in the datasheet). 100R series near the
Nucleo, 10k pull-down near J101: the gates stay off while the MCU is in reset.
TIM1 CH1..CH3 / CH1N..CH3N drive the LM5109B inputs HI/LI on the power board (TTL
ENABLE (J401): close the loop (switch or E-stop) to release TIM1_BKIN (PE15, active low).
Gate driver interface and enable

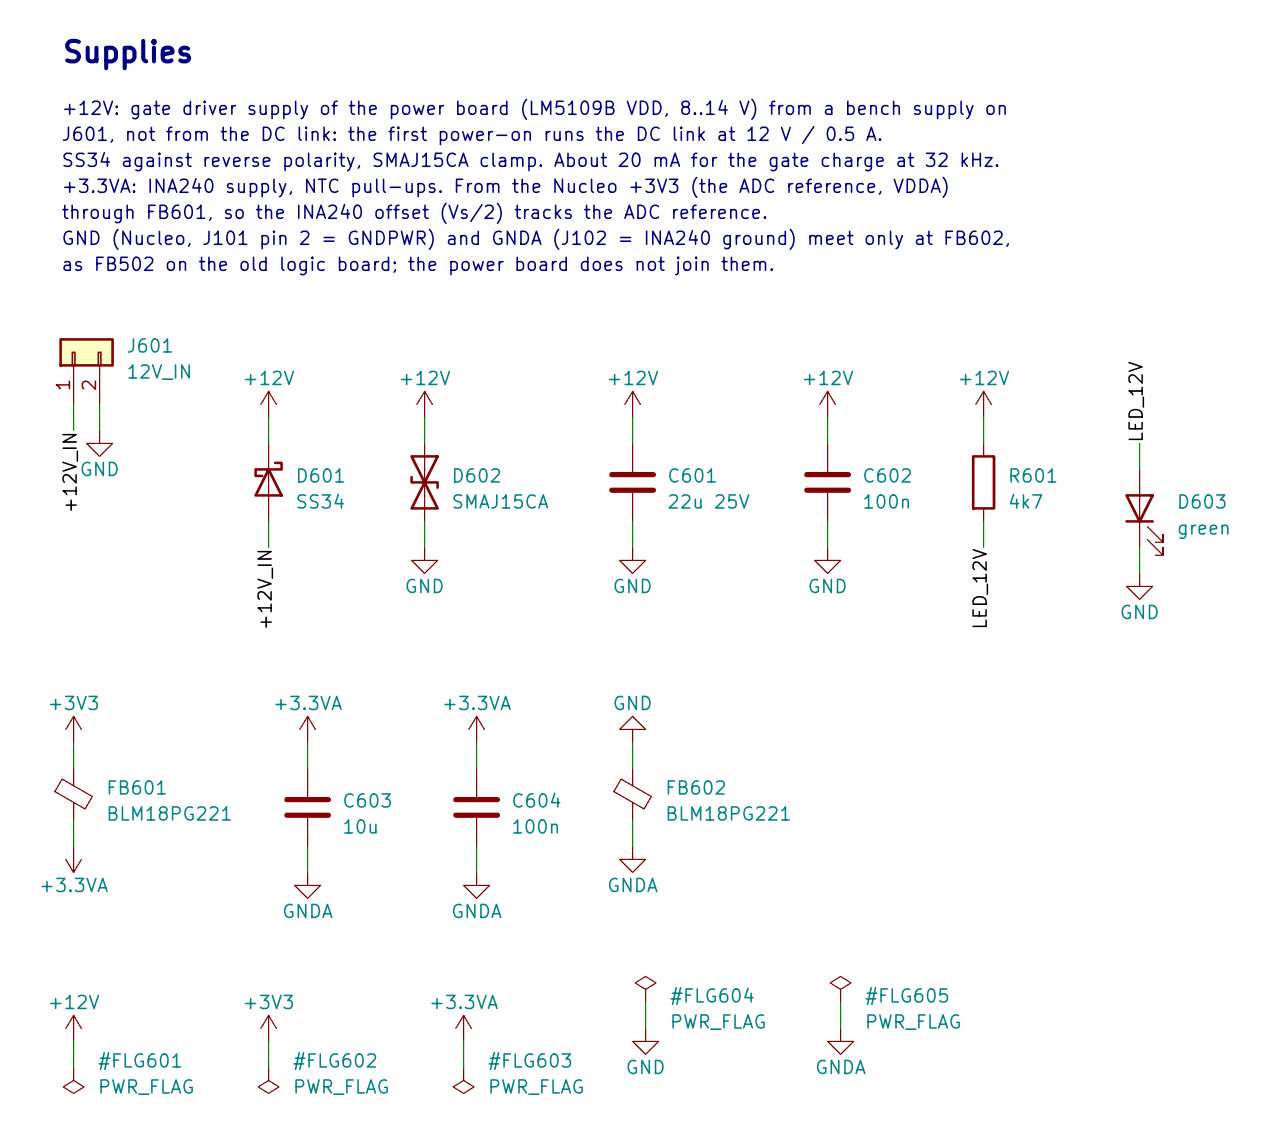
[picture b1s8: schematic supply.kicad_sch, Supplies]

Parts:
C601: 22u 25V; C_1206_3216Metric
C602, C604: 100n; C_0603_1608Metric
C603: 10u; C_0603_1608Metric
D601: SS34; D_SMA
D602: SMAJ15CA; D_SMA
D603: green; LED_0603_1608Metric
FB601, FB602: BLM18PG221; L_0603_1608Metric
J601: 12V_IN; TerminalBlock_Phoenix_MKDS-1,5-2-5.08_1x02_P5.08mm_Horizont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
R601: 4k7; R_0603_1608Metric

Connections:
+3.3VA: C603.1, C604.1, FB601.2; also elsewhere on the board
+3V3: FB601.1; also elsewhere on the board
+12V: C601.1, C602.1, D601.1 (K), D602.1 (A1), R601.1; also elsewhere on the board
/supply/+12V_IN: D601.2 (A), J601.1
/supply/LED_12V: D603.2 (A), R601.2
GND: C601.2, C602.2, D602.2 (A2), D603.1 (K), FB602.1, J601.2; also elsewhere on the board
GNDA: C603.2, C604.2, FB602.2; also elsewhere on the board

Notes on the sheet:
J601, not from the DC link: the first power-on runs the DC link at 12 V / 0.5 A.
GND (Nucleo, J101 pin 2 = GNDPWR) and GNDA (J102 = INA240 ground) meet only at FB602,
as FB502 on the old logic board; the power board does not join them.
+12V: gate driver supply of the power board (LM5109B VDD, 8..14 V) from a bench supply on
+3.3VA: INA240 supply, NTC pull-ups. From the Nucleo +3V3 (the ADC reference, VDDA)
SS34 against reverse polarity, SMAJ15CA clamp. About 20 mA for the gate charge at 32 kHz.
Supplies
through FB601, so the INA240 offset (Vs/2) tracks the ADC reference.

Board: 4 copper layers, 78 parts (2 on the bottom side), 54 nets, no tracks yet.

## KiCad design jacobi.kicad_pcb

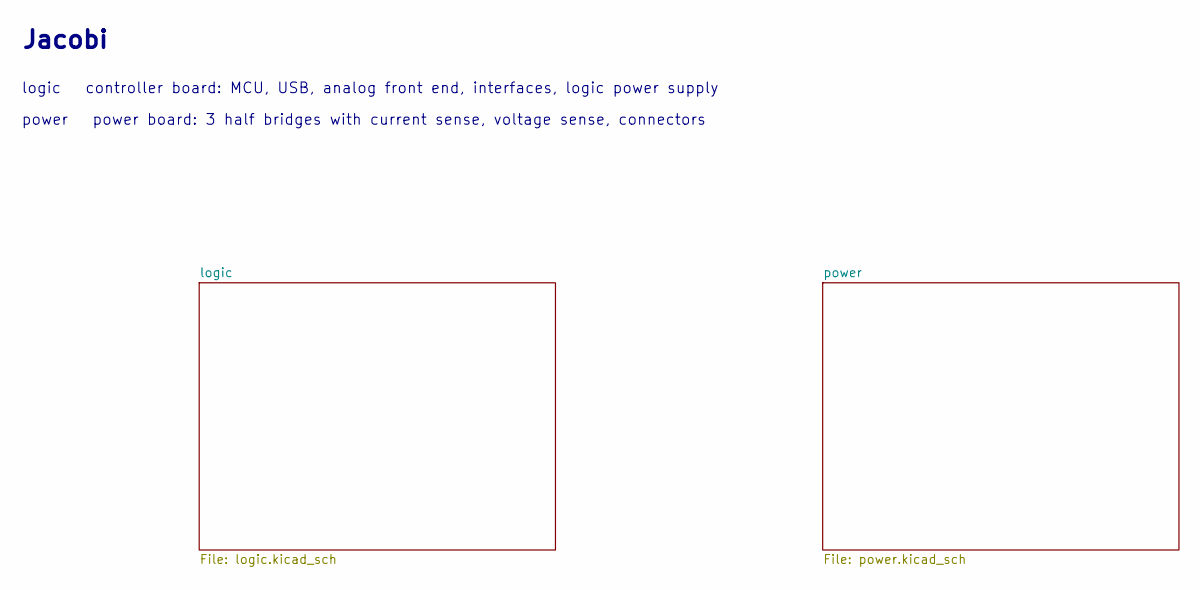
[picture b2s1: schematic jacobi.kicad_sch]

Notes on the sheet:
Jacobi
logic controller board: MCU, USB, analog front end, interfaces, logic power supply
power power board: 3 half bridges with current sense, voltage sense, connectors
